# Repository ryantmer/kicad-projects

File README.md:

# KiCad Projects

See title. Learning KiCAD, needed a place for stuff. So, here is that place, and here is that stuff.

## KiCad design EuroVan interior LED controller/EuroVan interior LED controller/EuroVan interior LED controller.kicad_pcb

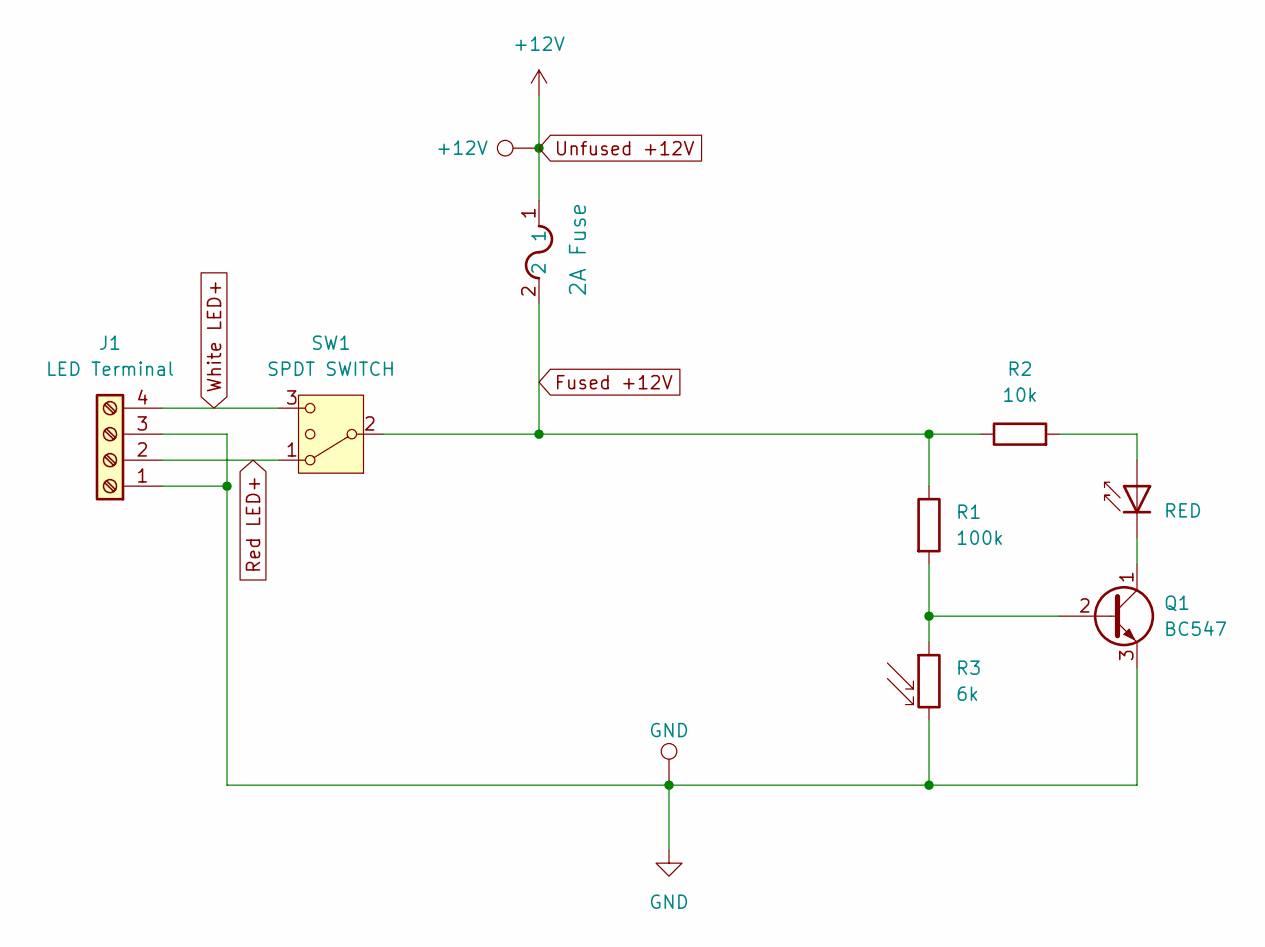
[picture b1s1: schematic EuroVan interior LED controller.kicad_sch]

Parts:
D1: RED; LED_D5.0mm_IRGrey
F1: 2A Fuse; Fuseholder_Cylinder-5x20mm_Stelvio-Kontek_PTF78_Horizontal_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
J1: LED Terminal; TerminalBlock_TE_282834-4_1x04_P2.54mm_Horizontal
Q1: BC547; TO-92_Inline
R1: 100k; R_Axial_DIN0207_L6.3mm_D2.5mm_P10.16mm_Horizontal
R2: 10k; R_Axial_DIN0207_L6.3mm_D2.5mm_P10.16mm_Horizontal
R3: 6k; R_LDR_4.9x4.2mm_P2.54mm_Vertical
SW1: SPDT SWITCH; PinHeader_1x03_P2.54mm_Vertical
TP1: +12V; Keystone 4919 PC quick connect terminal
TP2: GND; Keystone 4919 PC quick connect terminal

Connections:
Fused +12V: F1.2, R1.1, R2.1, SW1.2 (3)
GND: J1.1, J1.3, Q1.3 (E), R3.2, TP2.1
unnamed: D1.2 (A), R2.2
unnamed: D1.1 (K), Q1.1 (C)
unnamed: Q1.2 (B), R1.2, R3.1
Red LED+: J1.2, SW1.1
Unfused +12V: F1.1, TP1.1
White LED+: J1.4, SW1.3 (4)

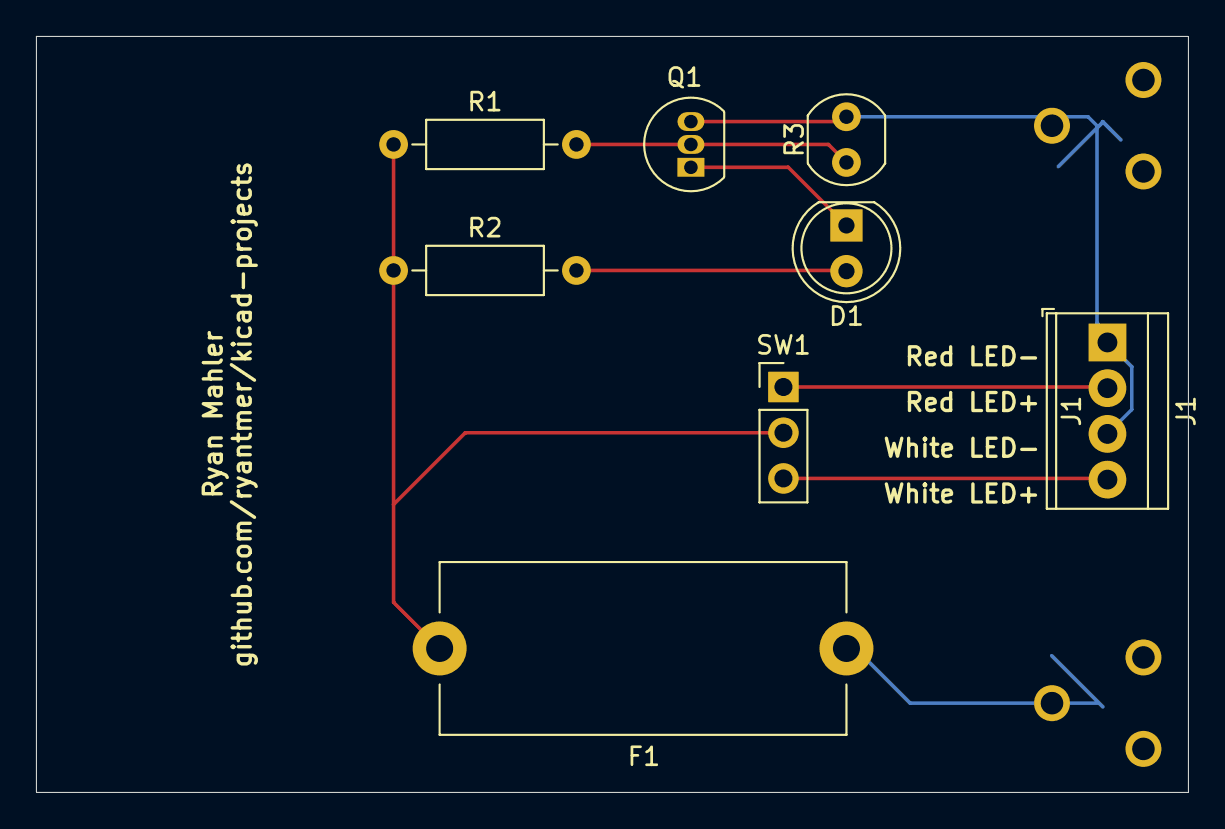
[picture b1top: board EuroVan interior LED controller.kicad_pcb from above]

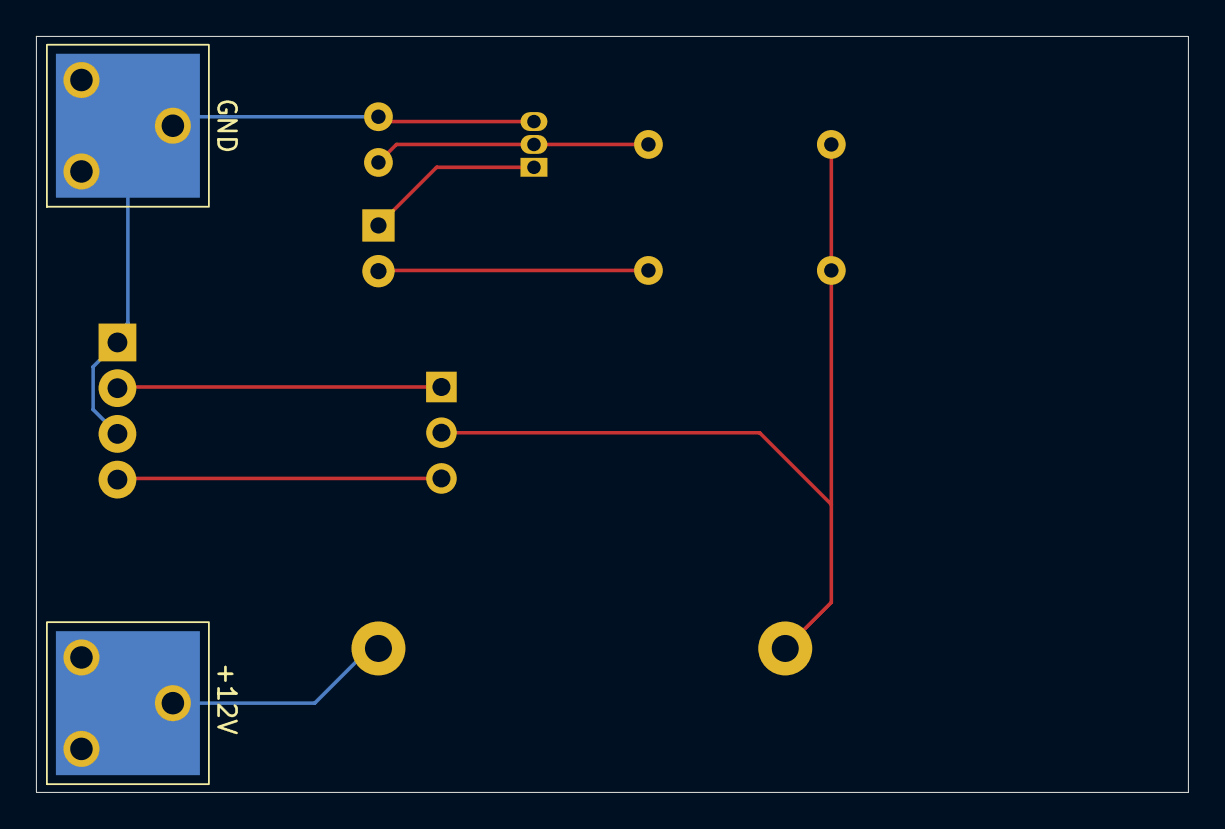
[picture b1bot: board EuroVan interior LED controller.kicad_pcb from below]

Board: 2 copper layers, 64.0 x 42.0 mm, 10 parts (2 on the bottom side), 8 nets.

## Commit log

2024-08-25 Initial commit
    Adds KiCAD files for EuroVan interior LED controller
2024-08-25 Add Gerber files
2024-08-31 Moved diagram to be centred, how a e s t h e t i c
2024-09-15 I turned a 360 into a 0
    I don't remember why. Or what this actually is.
